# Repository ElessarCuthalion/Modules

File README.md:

# Modules
 Small PCB modules: Sensors, Chargers, etc...

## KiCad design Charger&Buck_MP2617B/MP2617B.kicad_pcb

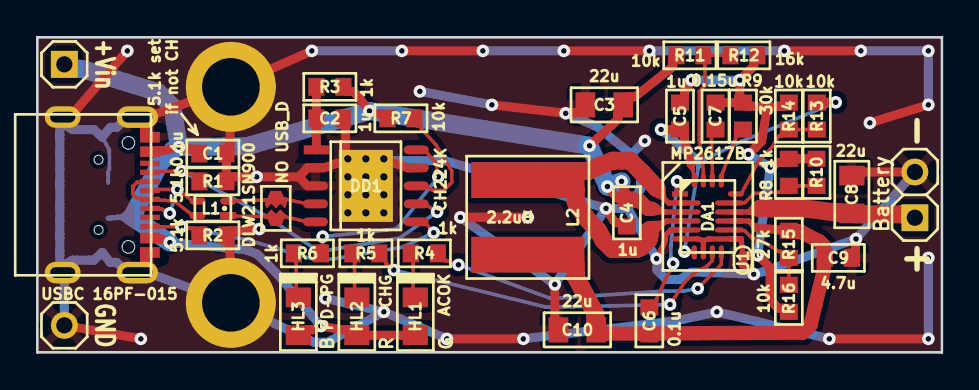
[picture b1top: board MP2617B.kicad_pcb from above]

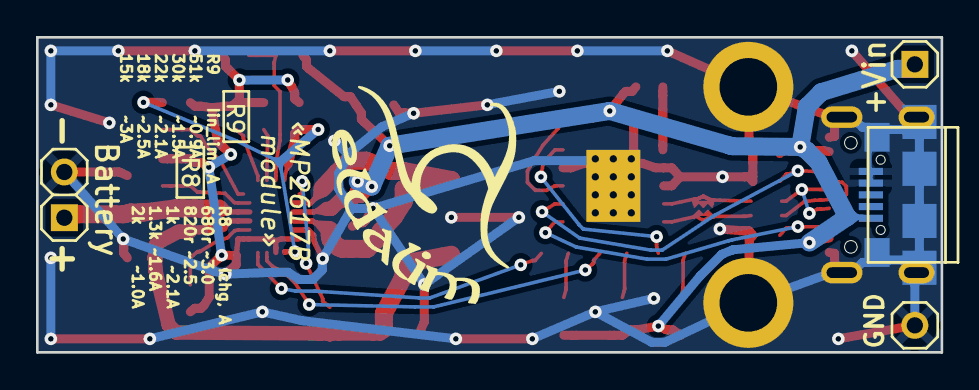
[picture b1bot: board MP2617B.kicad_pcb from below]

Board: 2 copper layers, 50.2 x 17.5 mm, 43 parts (2 on the bottom side), 29 nets.

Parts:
C1, C6: 0.1u; CAP0603
C2, C4, C5: 1u; CAP0603
C3, C8, C10: 22u; CAP0805
C7: 0.15u; CAP0603
C9: 4.7u; CAP0603
DA1: MP2617B; FCQFN20
DD1: CH224K; HESOP10
GB1: Battery; for_PolarOut_PLS-2
HL1: ACOK; LED0805
HL2: CHG; LED0805
HL3: PD-PG; LED0805
Hole1, Hole2: HoleMetalled; Hole_for_M3_small
J1: Jumper; Jump_0.5mm
L1: DLW21SN900; Choke_0805
L2: 2.2uH; IND_5.7x5.7_5D28
Logo1: Eldalim; Eldalim_12x10
R1, R2: 5.1k; RES0603
R3, R4, R5, R6, R8: 1k; RES0603
R7, R11, R13, R14, R16: 10k; RES0603
R9: 30k; RES0603
R10: DNP; RES0603
R12: 16k; RES0603
R15: 27k; RES0603
XP1: +Vin; PLS-1
XP2: GND; PLS-1Rnd
XS1: USBC 16PF-015; USB-C_16pin_16PF-015
XS2: USB-micro B; USB-micro_B
fus1: NO USB_D; FuseSolder

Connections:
+USBvcc: C1.1, C3.1, C4.1, DA1.3 (VIN), HL1.A, HL2.A, HL3.A, R3.1, R7.2, R11.1, XP1.1, XS1.A4B9, XS1.B4A9, XS2.1
+VCC: C6.2, C9.1, C10.1, DA1.13 (SYS), L2.2, R15.1
/+BATT: C8.1, DA1.14 (BATT), GB1.1 (+)
/+CH_VDD: C2.1, DD1.1 (VDD), R3.2
/+LX1: DA1.2 (SW), DA1.4 (SW), L2.1
/+MP_VCC: C5.1, DA1.7 (M0), DA1.20 (VCC)
/ACOK: DA1.10 (~ACOK), R4.2
/CHG: DA1.9 (~CHG), R5.2
/CH_DM: DD1.5 (DM), L1.1, fus1.2
/CH_DP: DD1.4 (DP), L1.4, fus1.1
/CH_PG: DD1.10 (PG), R6.2
/ILIM: DA1.17 (ILIM), R9.1
/NTC: DA1.16 (NTC), R13.2, R14.1
/SFB: DA1.12 (SFB), R15.2, R16.1
/USB_CC1: DD1.7 (CC1), R1.1, XS1.A5
/USB_CC2: DD1.6 (CC2), R2.1, XS1.B5
/USB_DM: L1.2, XS1.A7, XS1.B7
/USB_DP: L1.3, XS1.A6, XS1.B6
/VLIM: DA1.19 (VLIM), R11.2, R12.1
GND: C1.2, C2.2, C3.2, C4.2, C8.2, C9.2, C10.2, DA1.5 (PGND), DD1.PAD (GND), GB1.2 (-), Hole1.H, Hole2.H, J1.2, R1.2, R2.2, XP2.1, XS1.A1B12, XS1.B1A12, XS1.SHLD, XS2.4, XS2.5, XS2.SHLD
GNDL: C5.2, C7.2, DA1.6 (~EN), DA1.8 (M1), DA1.11 (AGND), J1.1, R8.2, R9.2, R10.2, R12.2, R14.2, R16.2
GNDP: DD1.2 (CFG2), DD1.3 (CFG3), DD1.9 (CFG1)
unnamed: C6.1, DA1.1 (BST)
unnamed: DA1.15 (ISET), R8.1, R10.1
unnamed: C7.1, DA1.18 (TMR)
unnamed: DD1.8 (Vbus), R7.1
unnamed: HL1.C, R4.1
unnamed: HL2.C, R5.1
unnamed: HL3.C, R6.1

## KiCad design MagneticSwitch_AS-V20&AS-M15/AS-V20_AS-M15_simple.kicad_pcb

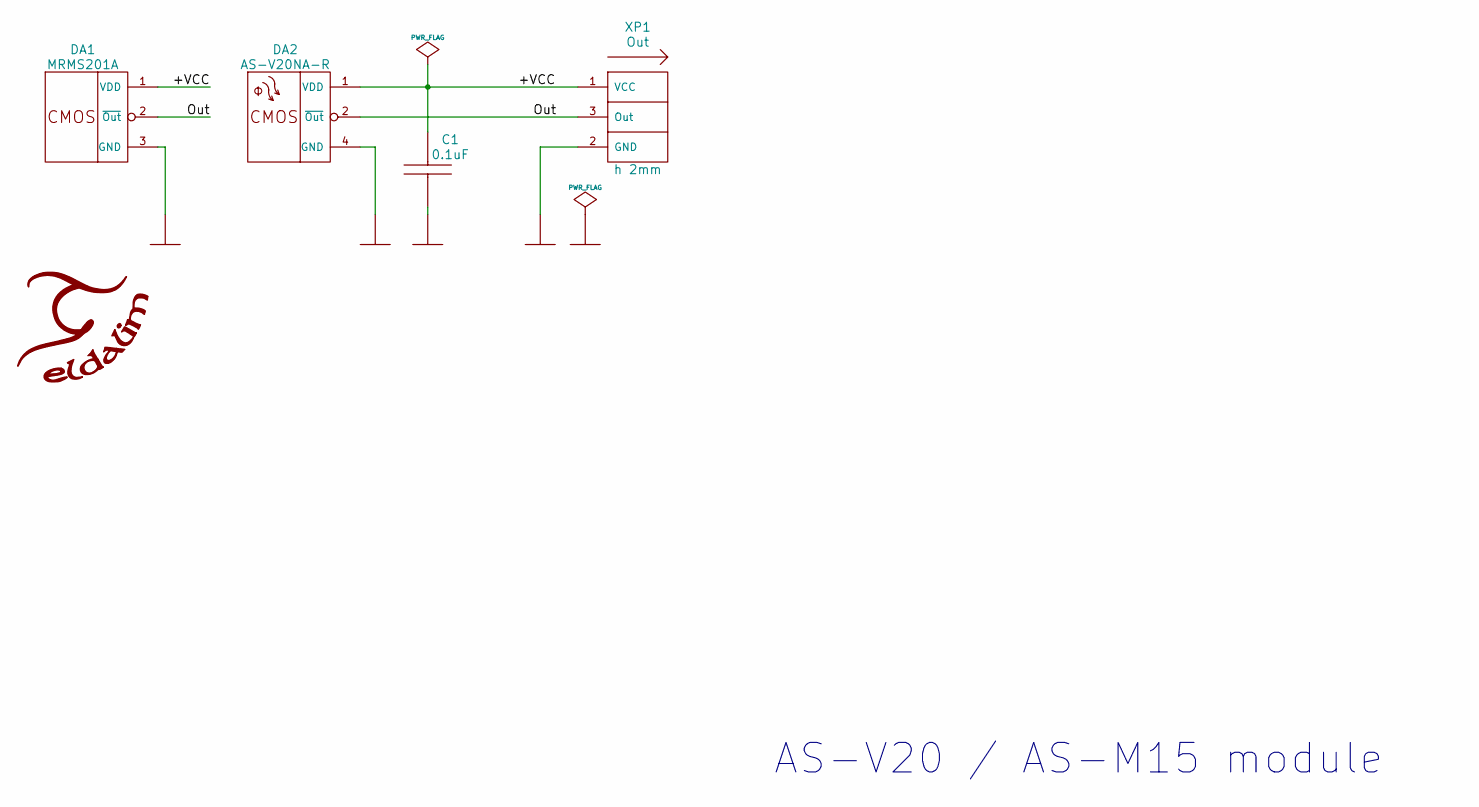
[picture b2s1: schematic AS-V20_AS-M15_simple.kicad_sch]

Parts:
C1: 0.1uF; CAP0603
DA1: MRMS201A; SOT23-3
DA2: AS-V20NA-R; SON4
Logo1: Eldalim; Eldalim_7x6_back
XP1: Out; for_SENS_PLS2-3

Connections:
/+VCC: C1.1, DA1.1 (VDD), DA2.1 (VDD), XP1.1 (VCC)
/Out: DA1.2 (~Out), DA2.2 (~Out), XP1.3 (Out)
GND: C1.2, DA1.3 (GND), DA2.4 (GND), XP1.2 (GND)

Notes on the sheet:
AS-V20 / AS-M15 module

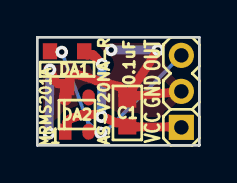
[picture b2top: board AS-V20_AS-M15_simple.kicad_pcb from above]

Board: 2 copper layers, 9.0 x 6.0 mm, 5 parts (0 on the bottom side), 3 nets.

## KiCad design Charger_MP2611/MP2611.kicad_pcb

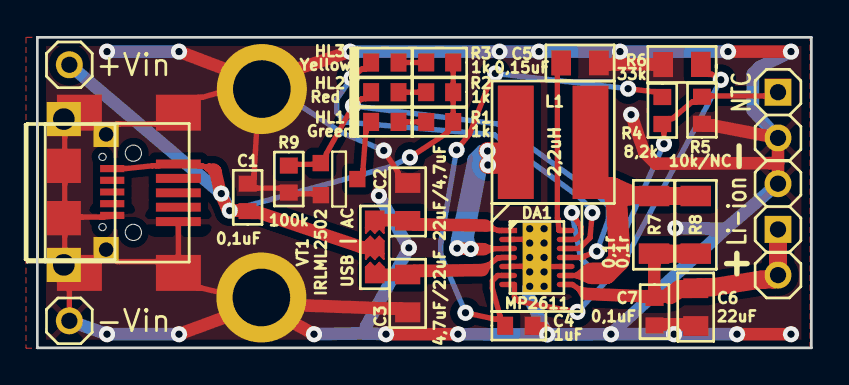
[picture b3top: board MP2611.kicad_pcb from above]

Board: 2 copper layers, 43.0 x 17.3 mm, 33 parts (1 on the bottom side), 17 nets.

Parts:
C1, C7: 0,1uF; CAP0603
C2: 22uF/4,7uF; CAP0805
C3: 4,7uF/22uF; CAP0805
C4: 1uF; CAP0603
C5: 0,15uF; CAP0805
C6: 22uF; CAP0805
DA1: MP2611; DFN14_3x4
GB1: Li-ion; PLS-2
HL1: Green; LED0603
HL2: Red; LED0603
HL3: Yellow; LED0603
HOLE1, HOLE2: HOLE_METALLED; Hole_for_M3_small
L1: 2,2uH; 5D28
Label1: Eldalim; Eldalim_17x15
R1, R2, R3: 1k; RES0603
R4: 8,2k; RES0603
R5: 10k/NC; RES0603
R6: 33k; RES0805
R7, R8: 0,1r; RES1206
R9: 100k; RES0603
VT1: IRLML2502; SOT23-3
XP1: +Vin; PLS-1Rnd
XP2: -Vin; PLS-1Rnd
XP3: NTC; PLS-2
XP4: Load; PLS-1Rnd
XS1: mini-USB; USB-mini_B
XS2: mcro-USB; USB-micro_B+Hole
fuse1: USB | AC; FuseSolder_x2_0603

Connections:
/ACin: C2.1, DA1.1, fuse1.2
/Batt: C6.1, C7.1, DA1.8, GB1.1, R7.2, R8.2, XP4.1
/LX1: DA1.3, L1.1
/LX2: DA1.9, L1.2, R7.1, R8.1
/NTC: DA1.13, R4.2, R5.2, XP3.1
/STAT1: DA1.11, HL2.C, R9.1, VT1.1
/STAT2: DA1.12, HL3.C
/USB_VCC: C1.1, R1.2, R2.1, R3.1, XP1.1, XS1.1, XS2.1, fuse1.1
/USBin: C3.1, DA1.4, fuse1.3
/Vfef: C4.1, DA1.6, R4.1
GND: C1.2, C2.2, C3.2, C4.2, C5.2, C6.2, C7.2, DA1.2, DA1.5, DA1.10, DA1.PAD, GB1.2, HOLE1.H, HOLE2.H, R5.1, R6.2, R9.2, VT1.2, XP2.1, XP3.2, XS1.5, XS1.SHLD, XS2.5, XS2.SHLD
unnamed: C5.1, DA1.14
unnamed: DA1.7, R6.1
unnamed: HL1.A, R1.1
unnamed: HL1.C, VT1.3
unnamed: HL2.A, R2.2
unnamed: HL3.A, R3.2

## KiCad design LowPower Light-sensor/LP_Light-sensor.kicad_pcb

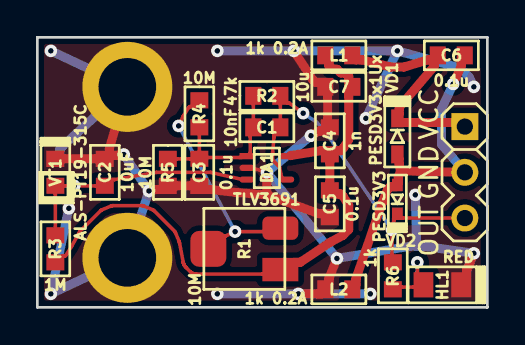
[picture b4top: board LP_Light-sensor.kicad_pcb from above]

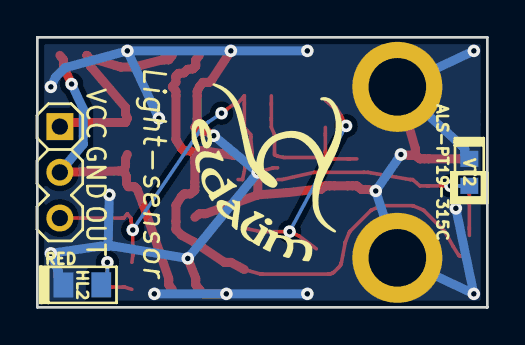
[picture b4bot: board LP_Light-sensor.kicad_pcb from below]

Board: 2 copper layers, 25.0 x 15.0 mm, 26 parts (3 on the bottom side), 9 nets.

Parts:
C1: 10nF; CAP0603
C2: 10uF; CAP0603
C3, C5, C6: 0.1u; CAP0603
C4: 1n; CAP0603
C7: 10u; CAP0603
DA1: TLV3691; SOT353
HL1, HL2: RED; LED0805
Hole1, Hole2: HoleMetalled; Hole_for_M3_small
L1, L2: 1k 0.2A; Bead_0603
Logo1: Eldalim; Eldalim_10x8
R1: 10M; RES_TRIM_Bourns3314J-1
R2: 47k; RES0603
R3: 1M; RES0603
R4, R5: 10M; RES0603
R6: 1k; RES0603
VD1: PESD3V3x1Ux; SOD323+523
VD2: PESD3V3x1UB; SOD523
VT1, VT2: ALS-PT19-315C; LightSens0603
XP1: SENS; for_SENS_PLS-3

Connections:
+VCC: C6.1, L1.1, VD1.C, XP1.1
/+LightSns_PWR: C4.1, C5.1, C7.1, DA1.5, L1.2, R1.1, R3.1
/LightSns_OUT: C1.2, DA1.4, R2.2, R6.1, VD2.C, XP1.3
/LightSns_Sign: C2.1, DA1.3, R3.2, VT1.C, VT2.C
GND: C2.2, C3.2, C4.2, C5.2, C7.2, DA1.2, HL1.C, HL2.C, Hole1.H, Hole2.H, L2.2, R5.2, VT1.E, VT2.E
GNDP: C6.2, L2.1, VD1.A, VD2.A, XP1.2
unnamed: C1.1, C3.1, DA1.1, R2.1, R4.2, R5.1
unnamed: HL1.A, HL2.A, R6.2
unnamed: R1.2, R1.3, R4.1

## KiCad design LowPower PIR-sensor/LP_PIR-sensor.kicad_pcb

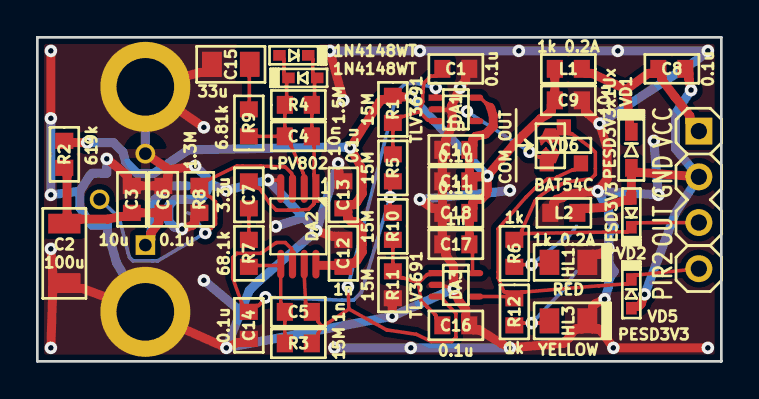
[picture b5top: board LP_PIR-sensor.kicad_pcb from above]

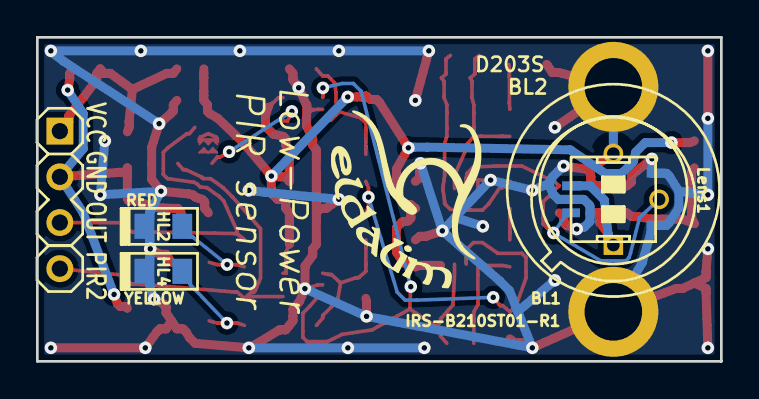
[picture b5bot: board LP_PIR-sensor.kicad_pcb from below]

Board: 2 copper layers, 38.0 x 18.0 mm, 54 parts (6 on the bottom side), 20 nets.

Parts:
BL1: IRS-B210ST01-R1; PIR_IRS-B210ST01
BL2: D203S; PIR_D203S_TO5-3
C1, C6, C8, C11, C13, C14, C16, C18: 0.1u; CAP0603
C2: 100u; CAP1206
C3, C9: 10u; CAP0603
C4: 10n; CAP0603
C5, C10, C12, C17: 1n; CAP0603
C7: 3.3u; CAP0603
C15: 33u; CAP0805
DA1, DA3: TLV3691; SOT353
DA2: LPV802; MSOP8
HL1, HL2: RED; LED0805
HL3, HL4: YELLOW; LED0805
Hole1, Hole2: HoleMetalled; Hole_for_M3_small
L1, L2: 1k 0.2A; Bead_0603
Lens1: Lens 8308-4; FresnelLens_10mm_8308-4
Logo1: Eldalim; Eldalim_10x8
R1, R3, R5, R10, R11: 15M; RES0603
R2: 619k; RES0603
R4: 1.5M; RES0603
R6, R12: 1k; RES0603
R7: 68.1k; RES0603
R8: 1.3M; RES0603
R9: 6.81k; RES0603
VD1: PESD3V3x1Ux; SOD323+523
VD2, VD5: PESD3V3x1UB; SOD523
VD3, VD4: 1N4148WT; SOD523
VD6: BAT54C; SOT23-3
XP1: SENS; for_SENS_PLS-3
XP2: PIR2; PLS-1Rnd
fus1: COM OUT; FuseSolder

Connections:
+VCC: C8.1, L1.1, VD1.C, XP1.1
/+PIR_PWR: C9.1, C10.1, C11.1, C12.1, C13.1, C17.1, C18.1, DA1.5, DA2.8, DA3.5, L1.2, R1.1, R2.1
/+PIR_PWR2: BL1.1, BL2.1, C2.1, C3.1, C6.1, R2.2
/PIR1: DA1.4, VD6.1, fus1.2
/PIR2: DA3.4, R12.1, VD5.C, VD6.2, XP2.1
/PIR_OUT: R6.1, VD2.C, VD6.3, XP1.3, fus1.1
/PIR_signal: BL1.3, BL2.2, DA2.3, R8.1
GND: BL1.2, BL1.4, BL1.5, BL2.3, C1.1, C2.2, C3.2, C6.2, C9.2, C10.2, C11.2, C12.2, C13.2, C14.2, C15.2, C16.2, C17.2, C18.2, DA1.2, DA2.4, DA3.2, HL1.C, HL2.C, HL3.C, HL4.C, Hole1.H, Hole2.H, L2.2, R8.2, R11.2
GNDP: C8.2, L2.1, VD1.A, VD2.A, VD5.A, XP1.2
unnamed: C1.2, DA1.3, R1.2, R5.1
unnamed: C4.1, DA2.2, R4.1, R9.1, VD3.C, VD4.A
unnamed: C4.2, C7.1, DA2.1, R4.2, VD3.A, VD4.C
unnamed: C5.1, DA2.5, R3.1, R7.2
unnamed: C5.2, DA1.1, DA2.7, DA3.3, R3.2
unnamed: C7.2, R7.1
unnamed: C14.1, DA2.6, R5.2, R10.1
unnamed: C15.1, R9.2
unnamed: C16.1, DA3.1, R10.2, R11.1
unnamed: HL1.A, HL2.A, R6.2
unnamed: HL3.A, HL4.A, R12.2

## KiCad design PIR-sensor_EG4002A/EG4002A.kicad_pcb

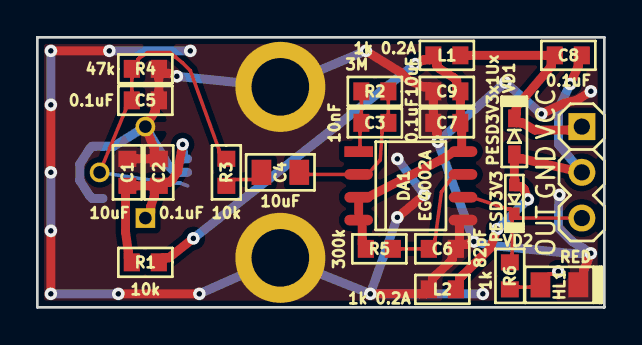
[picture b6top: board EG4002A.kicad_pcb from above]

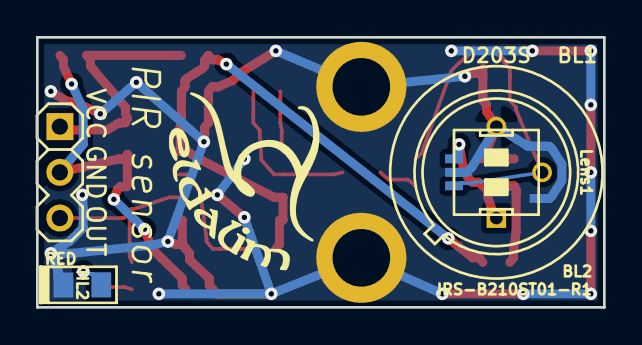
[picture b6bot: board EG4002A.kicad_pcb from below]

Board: 2 copper layers, 31.5 x 15.0 mm, 29 parts (5 on the bottom side), 12 nets.

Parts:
BL1: D203S; PIR_D203S_TO5-3
BL2: IRS-B210ST01-R1; PIR_IRS-B210ST01
C1, C9: 10uF; CAP0603
C2, C5, C7, C8: 0.1uF; CAP0603
C3: 10nF; CAP0603
C4: 10uF; CAP0805
C6: 82pF; CAP0603
DA1: EG4002A; SOP8
HL1, HL2: RED; LED0805
Hole1, Hole2: HoleMetalled; Hole_for_M3_small
L1, L2: 1k 0.2A; Bead_0603
Lens1: Lens 8308-4; FresnelLens_10mm_8308-4
Logo1: Eldalim; Eldalim_10x8
R1, R3: 10k; RES0603
R2: 3M; RES0603
R4: 47k; RES0603
R5: 300k; RES0603
R6: 1k; RES0603
VD1: PESD3V3x1Ux; SOD323+523
VD2: PESD3V3x1UB; SOD523
XP1: SENS; for_SENS_PLS-3

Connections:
+VCC: C8.1, L1.1, VD1.C, XP1.1
/+PIR_PWR: C7.2, C9.1, DA1.3, DA1.4, DA1.8, L1.2, R1.1, R5.2
/+PIR_PWR2: BL1.1, BL2.1, C1.1, C2.1, R1.2
/GND_in: C8.2, L2.1, VD1.A, VD2.A, XP1.2
/PIR_OUT: DA1.6, R6.1, VD2.C, XP1.3
/PIR_signal: BL1.2, BL2.3, C5.1, R3.1, R4.1
GND: BL1.3, BL2.2, BL2.4, BL2.5, C1.2, C2.2, C5.2, C6.2, C7.1, C9.2, DA1.5, HL1.C, HL2.C, Hole1.H, Hole2.H, L2.2, R4.2
unnamed: C3.1, C4.2, DA1.2, R2.1
unnamed: C3.2, DA1.1, R2.2
unnamed: C4.1, R3.2
unnamed: C6.1, DA1.7, R5.1
unnamed: HL1.A, HL2.A, R6.2

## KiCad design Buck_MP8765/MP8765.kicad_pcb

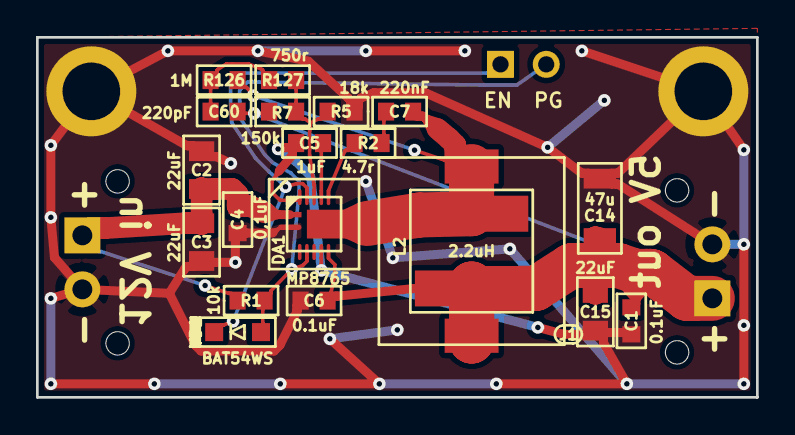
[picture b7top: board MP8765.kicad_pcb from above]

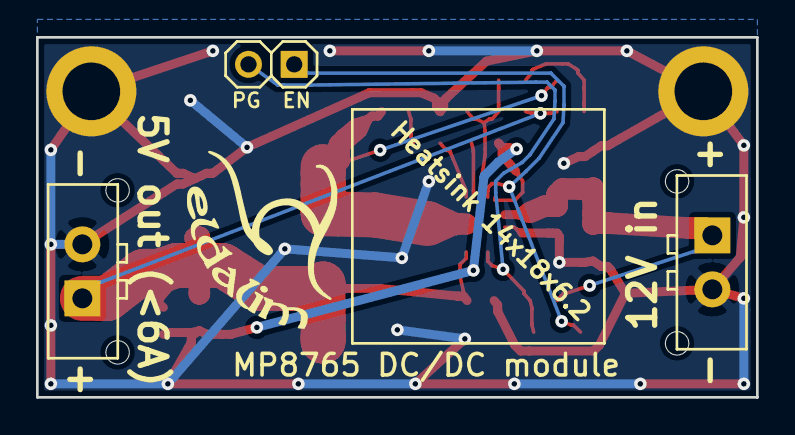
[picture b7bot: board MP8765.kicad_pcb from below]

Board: 2 copper layers, 40.0 x 20.0 mm, 28 parts (5 on the bottom side), 12 nets.

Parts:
C1, C6: 0.1uF; CAP0603
C2, C3, C15: 22uF; CAP0805
C4: 0,1uF; CAP0603
C5: 1uF; CAP0603
C7: 220nF; CAP0603
C14: 47u; CAP1206
C60: 220pF; CAP0603
DA1: MP8765; HFCQFN16
Heat1: Heatsink 14x18x6.2; Heatsink_14x13(18)x6.2
Hole1, Hole2: HoleMetalled; Hole_for_M3_small
J1: Jumper; Jump_0.5mm
L2: 2.2uH; IND_10.3x10.4_CDRH104
L65: IND_5.7x5.7_5D28
Logo1: Eldalim; Eldalim_10x8
R1: 10k; RES0603
R2: 4.7r; RES0603
R5: 18k; RES0603
R7: 150k; RES0603
R126: 1M; RES0603
R127: 750r; RES0603
VD1: BAT54WS; SOD323
XP1: 12V in; for_PolarOut_MicroFit-1x2
XP2: 5V out (<6A); for_PolarOut_MicroFit-1x2
XP3: PG EN; PLS-2

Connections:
+5Vout: C1.1, C6.1, C14.1, C15.1, C60.2, DA1.7, L2.2, L65.2, R7.1, XP2.1
+12V: C2.1, C3.1, C4.1, DA1.1, R1.1, XP1.1
/5Vout_Good: DA1.4, R1.2, VD1.A, XP3.2
/+SW1: C7.2, DA1.8, DA1.9, L2.1, L65.1, R126.1
/Enadle: DA1.13, VD1.C, XP3.1
GND: C1.2, C2.2, C3.2, C4.2, C6.2, C14.2, C15.2, DA1.2, Hole1.H, Hole2.H, J1.2, R5.1, XP1.2, XP2.2
GNDL1: C5.2, DA1.6, DA1.14, J1.1
unnamed: C5.1, DA1.11
unnamed: C7.1, R2.2
unnamed: C60.1, R126.2, R127.1
unnamed: DA1.10, R2.1
unnamed: DA1.12, R5.2, R7.2, R127.2

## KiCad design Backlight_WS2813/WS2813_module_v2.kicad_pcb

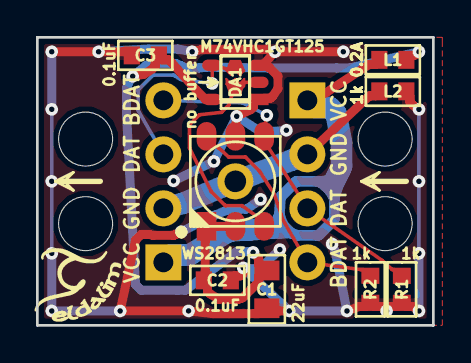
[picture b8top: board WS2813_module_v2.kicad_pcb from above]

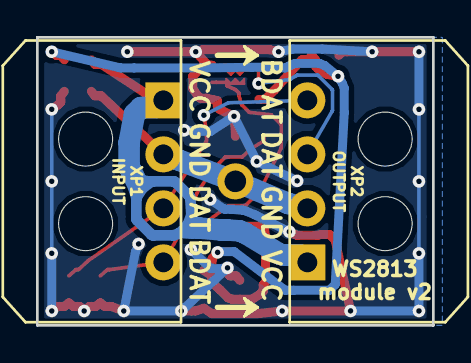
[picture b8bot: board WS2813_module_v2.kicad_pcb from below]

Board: 2 copper layers, 22.0 x 16.0 mm, 14 parts (2 on the bottom side), 8 nets.

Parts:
C1: 22uF; CAP0805
C2, C3: 0.1uF; CAP0603
DA1: M74VHC1GT125; SOT23-5
HL1: WS2813
Hole1: HoleMetalled; Hole_for_M2
L1, L2: 1k 0.2A; IND0603
Logo1: Eldalim; Eldalim_5x4
R1, R2: 1k; RES0603
XP1: INPUT; for_WS2813_MicroFit-1x4R
XP2: OUTPUT; for_WS2813_MicroFit-1x4R
fus1: no buffer; FuseSolder

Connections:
+VCC: C1.1, C2.1, C3.1, DA1.5, HL1.1, HL1.2, L1.2
+VCCin: L1.1, XP1.1, XP2.1
/BDin: HL1.6, R2.1, XP1.4
/Din: HL1.4, R1.1, XP1.3, XP2.4
/Dout: DA1.4, XP2.3, fus1.2
GND: C1.2, C2.2, C3.2, DA1.1, DA1.3, HL1.5, L2.2, R1.2, R2.2
GNDP: Hole1.H, L2.1, XP1.2, XP2.2
unnamed: DA1.2, HL1.3, fus1.1

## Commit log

2018-01-26 + WS2813 single
2018-02-14 MP2637: +SCHEMATIC
2018-02-24 MP2637: засстановка компонентов...
2018-02-24 MP2637: расстановка компонентов завершена
2018-03-09 MP2637: Трассировка завершена
2018-03-11 MP2637: проектировка завершена
2018-10-27 + AS-V20_AS-M15_invert_cover
2018-11-13 вариант WS2813_single: с обжимными разъёмамы "плата-провод" (начата работа)
2019-01-30 + WS2813 v2
2019-01-30 + gerber
2019-02-03 + WS2813_single_side_conn
2019-02-19 WS2813_single_side_conn_small - запрос в Телерем
2019-03-01 обновлены файлы
2019-03-15 Обновлены гербер-файлы
2019-11-13 миграция из репозитория CleverChandelier
2019-11-15 + заготовка для корпуса WS2813_module_v2
2020-02-21 + 3D
2020-06-05 + MP8765 module (схема готова, компоненты расставлены)
2020-06-06 модуль MP8765 завершён
2020-06-08 +3D MP8765
2020-06-20 обновлён MP2611
2020-06-28 + результаты тестов и правки
2020-11-17 MP2611 - обновлён контур платы
2021-03-14 обновлены модели простого магнито-резистивного датчика
2022-07-12 смена кодировки
2022-09-22 Переоткрыты схемы
2022-09-22 Добавлен PIR-модуль EG4002A
2022-09-23 довавлен Low-Power PIR sensor
2022-09-23 Low-Power Light-sensor: первый вариант схемы, расстановка компонентов
2022-09-24 Датчик освещённости: работа завершена
2023-06-25 MP2611: переход на KiCad 7 + комментарий в схеме
2024-01-30 AS-V20_AS-M15_simple: переход на KiCad 7
2024-01-30 AS-V20_AS-M15_simple: правка настроек
2024-01-30 Начата работа над модулем featuref/MP2617B
2024-02-01 добавлена цепь Vsys_FB
2024-02-04 Основная схема завершена
2024-02-05 +USB type-C & Power Delivery
2024-02-06 компоненты расставлены
2024-02-06 трассирровка завершкна, шелкография сделана.
2024-02-09 комментарий
2024-09-17 исправления и дополнения
2024-11-01 заметки
